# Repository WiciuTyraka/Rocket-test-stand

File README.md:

# Rocket test stand

## About
This is a project of rocket test stand to measure the trust and temperature of the engine and to save the data on SD-card. In nearly future I will add a wireless communication with computer to collect and proces data in real time. To wireless communication i will use a LoRa module.

- [Rocket test stand](#rocket-test-stand)
  * [About](#about)
  *  [PCB](#pcb)
      - [Schema](#schema)
      - [Board](#board)
      - [Libraries](#libraries)
  * [Sensors](#sensors)
      - [SD-card](#sd-card)
      - [Load cell and HX711](#load-cell-and-hx711)
      - [Thermocouples and max6675](#thermocouples-and-max6675)
      - [LoRa module](#lora-module)
      - [Pin map](#pin-map)
  * [Code for arduino](#code-for-arduino)
  * [Code for STM32](#code-for-stm32)

## PCB
Circut board is designed in Eagle

### Schema
 Rocket test stend consist of two board.
 - First board is a shield for Arduino Uno or STM32 Nucelo board. On this board is located a adpter for SD-card, amplifire for load cell and thermometr, and also a LoRa module.<br/>
[schema of rocket test stand board](https://github.com/WiciuTyraka/Rocket-test-stand/blob/master/PCB/Schema/Rocekt_test_stand.sch)

- Second board is used to collecting signals from sensors and ignite the engine.<br/>
[schema of input rocket test stand board](https://github.com/WiciuTyraka/Rocket-test-stand/blob/master/PCB/Schema/Rocekt_test_stand_input.sch)

### Board
links for downloading a board file.
- [link for rocket_test_stend.brd](https://github.com/WiciuTyraka/Rocket-test-stand/blob/master/PCB/Board/Rocekt_test_stand.brd)
- [link for rocket_test_stend_input.brd](https://github.com/WiciuTyraka/Rocket-test-stand/blob/master/PCB/Board/Rocekt_test_stand_input.brd)

### Libraries
Here are a necessary libraries for elements thats are used in project.
- [ark 8.5mm](https://github.com/WiciuTyraka/Rocket-test-stand/blob/master/PCB/Lib/111_ark_8.5mm.lbr)
- [hx711](https://github.com/WiciuTyraka/Rocket-test-stand/blob/master/PCB/Lib/111_hx711.lbr)
- [LoRa module](https://github.com/WiciuTyraka/Rocket-test-stand/blob/master/PCB/Lib/111_LORA.lbr)
- [max6675](https://github.com/WiciuTyraka/Rocket-test-stand/blob/master/PCB/Lib/111_max6675.lbr)
- [microsd](https://github.com/WiciuTyraka/Rocket-test-stand/blob/master/PCB/Lib/111_microsd.lbr)

## Sensors
In this project are used few sensors and device, here you can find a exemple code, libraries and datasheet for them.

### SD-card
---
Micro sd-card adapter is used for saving all data in txt file or as a json.
<details>
<summary>details</summary>
</br>

#### Wireing schema
This is the schema for all the wireing with arduino

#### Adapter wireing
| MicroSD Card Adapter | Adruino UNO Pin |
|----------------------|----------------:|
|          CS          |        4        |
|          SCK         |        13       |
|          MOSI        |        11       |
|          MISO        |        12       |
|          VCC         |        5V       |
|          GND         |        GND      |

#### Arduino code
[the necessary code is here](https://github.com/WiciuTyraka/Rocket-test-stand/blob/master/Sensors/SD-card/save_to_file/save_to_file.ino)
</details>

### Load cell and HX711
---
Load cell id used for measuring a engine thrust. Analog signal form load cell is converting to digital by HX711 amplifier
<details>
<summary>details</summary>
</br>
I cant find a datasheet for my chinese load cell so made this table

#### Basic load resistance checks
| Resistance check | Typical 350 Ω |
|------------------|--------------:|
| Ex+ to Ex-       | ~410Ω         |
| S+ to S-         | 350Ω          |
| Ex+ to S+        | ~315Ω         |
| Ex+ to S-        | ~315Ω         |
| Ex- to S+        | ~280Ω         |
| Ex- to S-        | ~280Ω         |

#### Load cell wireing
| HX711 | Load cell |
|-------|----------:|
| E+    | white     |
| E-    | red       |
| S+    | black     |
| S-    | green     |

#### Amplifer schema
This is a schema for all the wireing with arduino

#### HX711 library
You can download the necessary library here:
[download](https://halckemy.s3.amazonaws.com/uploads/attachments/392655/HX711-master.zip)

#### Arduino code
All the code necessary for calibration the load cell and measuring the force:
- calibration:
[the code is here](https://github.com/WiciuTyraka/Rocket-test-stand/blob/master/Sensors/Load_cell/calibration/calibration.ino)
- measurment:
[the code is here](https://github.com/WiciuTyraka/Rocket-test-stand/blob/master/Sensors/Load_cell/measurment/measurment.ino)

#### Datasheet
[link](https://circuits4you.com/wp-content/uploads/2016/11/hx711_datasheet_english.pdf)
</details>

### Thermocouples and max6675
---
To measure a temperature of the combustion chember and nozzle I'm using a thermocouple. Analog signal from this sensor is converting to digital by max6675 amplifier

<details>
<summary>details</summary>
</br>

#### Specifications of max6675
|                        |                    |
|------------------------|-------------------:|
| Suply Voltage          | 3.3 to 5 VDC       |
| Operating Current      | ~50mA              |
| Measurement Range      | 0 - 1024^∘C        |
| Measurement Resolution | +/- 0.25^∘C        |
| Output                 | Uses SPI interface |
| Required sensor        | K Thermocouple     |

#### Thermocouples schema
This is the schema for all the wireing with arduino

#### MAX6675 library
You can download the necessary library here:
[download](https://github.com/adafruit/MAX6675-library)

#### Arduino code
Basic code for reading temperature
[the necessary code is here](https://github.com/WiciuTyraka/Rocket-test-stand/blob/master/Sensors/Thermocouple/thermocouples/thermocouples.ino)

#### Datasheet
[link](http://henrysbench.capnfatz.com/wp-content/uploads/2015/05/MAX6675-Datasheet.pdf)

</details>

### LoRa module
---
I used LoRa transceiver to ignite the engine from safe distance also wireless communication allows me to watch data in real time.

<details>
<summary>details</summary>
</br>

The chip I used in project is a RFM95W transceiver.
The  RFM95W transceivers  feature  the  LoRaTM  long range modem that provides ultra-long range spread spectrum communication and high interference immunity whilst minimising current consumption.

#### RFM95W schema
This is the schema for all the wireing with arduino

#### RFM95W library
You can download the necessary library here:
[download](https://github.com/PaulStoffregen/RadioHead)

#### Arduino code
Here is a code for a transmiter and reciver(in fact both of them are transceivers) :
- transmiter:
[the code is here](https://github.com/WiciuTyraka/Rocket-test-stand/blob/master/Sensors/LoRa/transmiter/transmiter.ino)
- reciver:
[the code is here](https://github.com/WiciuTyraka/Rocket-test-stand/blob/master/Sensors/LoRa/reciver/reciver.ino)

#### Datasheet
[link](https://www.hoperf.com/modules/lora/RFM95.html)

</details>

### Pin map
---
This table contains information abaout all pins to witch are connected device

| Pin number |Device     |
|------------|---------- |
| 0          |LoRa DIO0  |
| 1          |LoRa DIO1  |
| 2          |HX711 CLK  |
| 3          |HX711 DOUT |
| 4          |SD card    |
| 5          |LoRa RESET |
| 6          |LoRa CS    |
| 8          |max6675 CS |
| 9          |max6675 SO |
| 10         |max6675 SCK|
| 11         |MOSI       |
| 12         |MISO       |
| 13         |CLK        |
| 14         |switch     |
| 15         |led        |
| 16         |ignite     |
| 17         |buzzer     |

## Code for Arduino

This version of code not include a wireless communication
- here you can find a [code](https://github.com/WiciuTyraka/Rocket-test-stand/blob/master/Arduino_code/Rocekt_test_stand/Rocekt_test_stand.ino)

## Code for STM32
cause i'm very busy right now, i'll back to this task in nearly future.

*by* Wiktor Tasarek

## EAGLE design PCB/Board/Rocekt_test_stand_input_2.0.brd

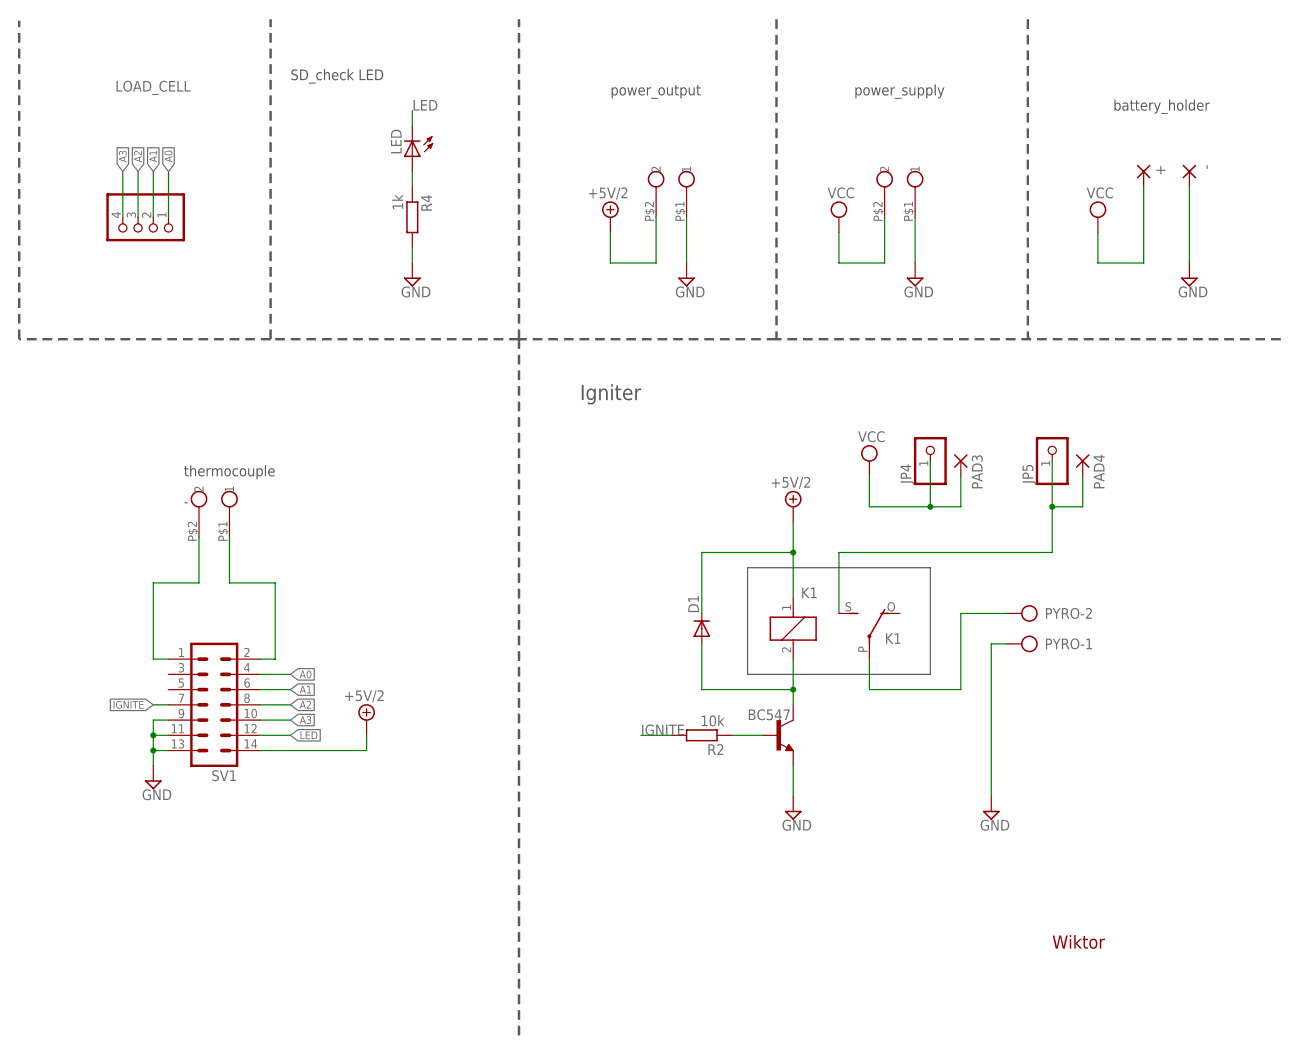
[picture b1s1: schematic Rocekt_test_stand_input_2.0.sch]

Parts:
+: SMD5; SMD2,54-5,08
-: SMD5; SMD2,54-5,08
D1: 1N4004; DO41-10
JP4, JP5: PINHD-1X1; 1X01
K1: G5L; G5LE
LED: LED_ELD260; LED_LD260
LOAD_CELL: PINHD-1X4; 1X04
PAD3, PAD4: SMD2; SMD1,27-2,54
POWER_SUPPLY, POWER_SUPPLY1: ARK_8.5MM; ZLACZESRUBOWE8.5MM
PYRO: AK500/2
R2: 10k; 0204/5
R4: 1k; 0204/5
SV1: ML14
T1: BC547; TO92
U$1: ARK_8.5MM; ZLACZESRUBOWE8.5MM

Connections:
+5V/2: D1.C, K1.1, POWER_SUPPLY1.P$2 (2), SV1.14
-: SV1.1, U$1.P$2 (2)
A0: LOAD_CELL.1, SV1.4
A1: LOAD_CELL.2, SV1.6
A2: LOAD_CELL.3, SV1.8
A3: LOAD_CELL.4, SV1.10
GND: -.1, POWER_SUPPLY.P$1 (1), POWER_SUPPLY1.P$1 (1), PYRO.1, R4.2, SV1.9, SV1.11, SV1.13, T1.1 (E)
IGNITE: R2.2, SV1.7
LED: LED.K (C), SV1.12
unnamed: D1.A, K1.2, T1.3 (C)
unnamed: R2.1, T1.2 (B)
unnamed: K1.P, PYRO.2
unnamed: SV1.2, U$1.P$1 (1)
unnamed: LED.A, R4.1
unnamed: JP5.1, K1.S, PAD4.1
VCC: +.1, JP4.1, PAD3.1, POWER_SUPPLY.P$2 (2)

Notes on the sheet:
thermocouple
power_supply
Wiktor
battery_holder
power_output
SD_check LED
Igniter

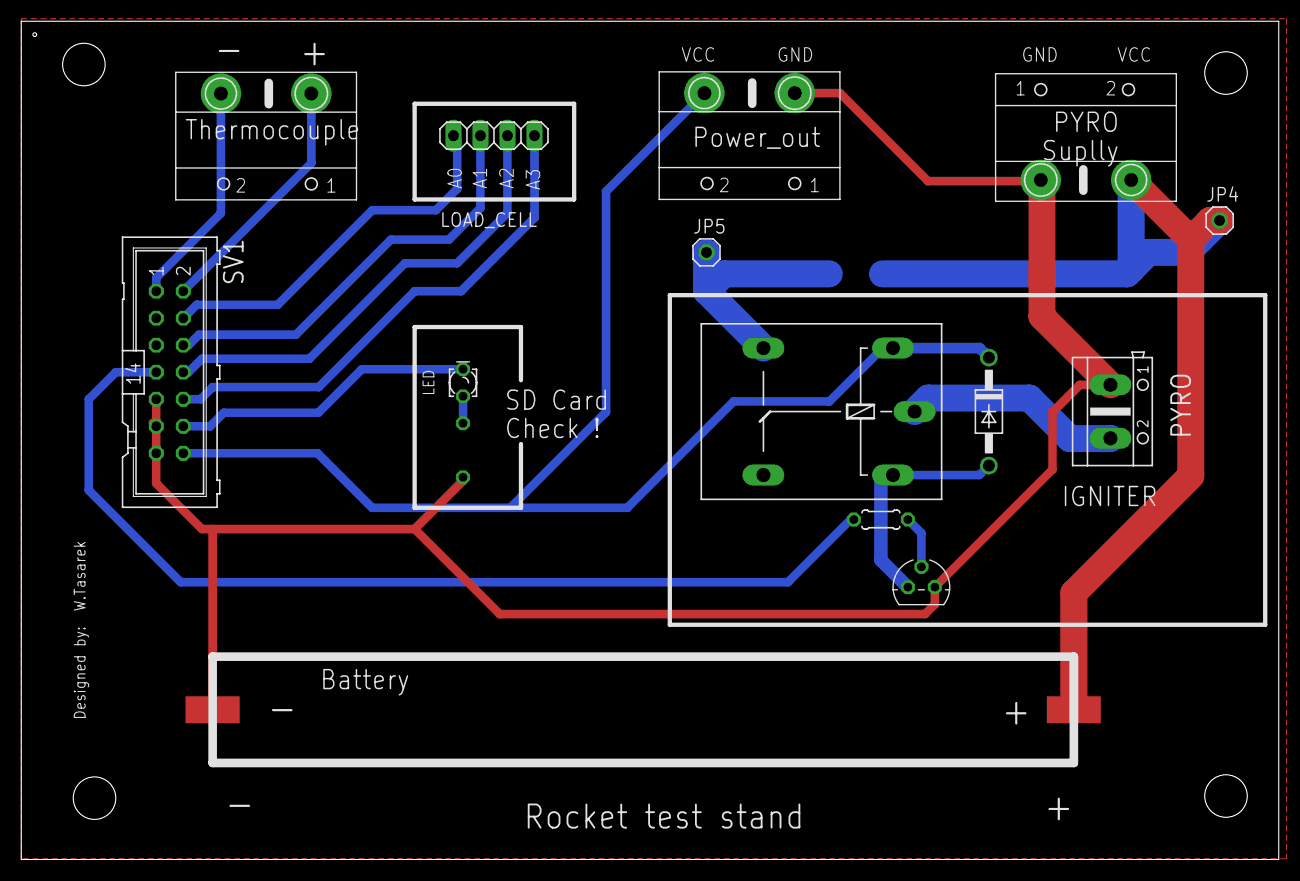
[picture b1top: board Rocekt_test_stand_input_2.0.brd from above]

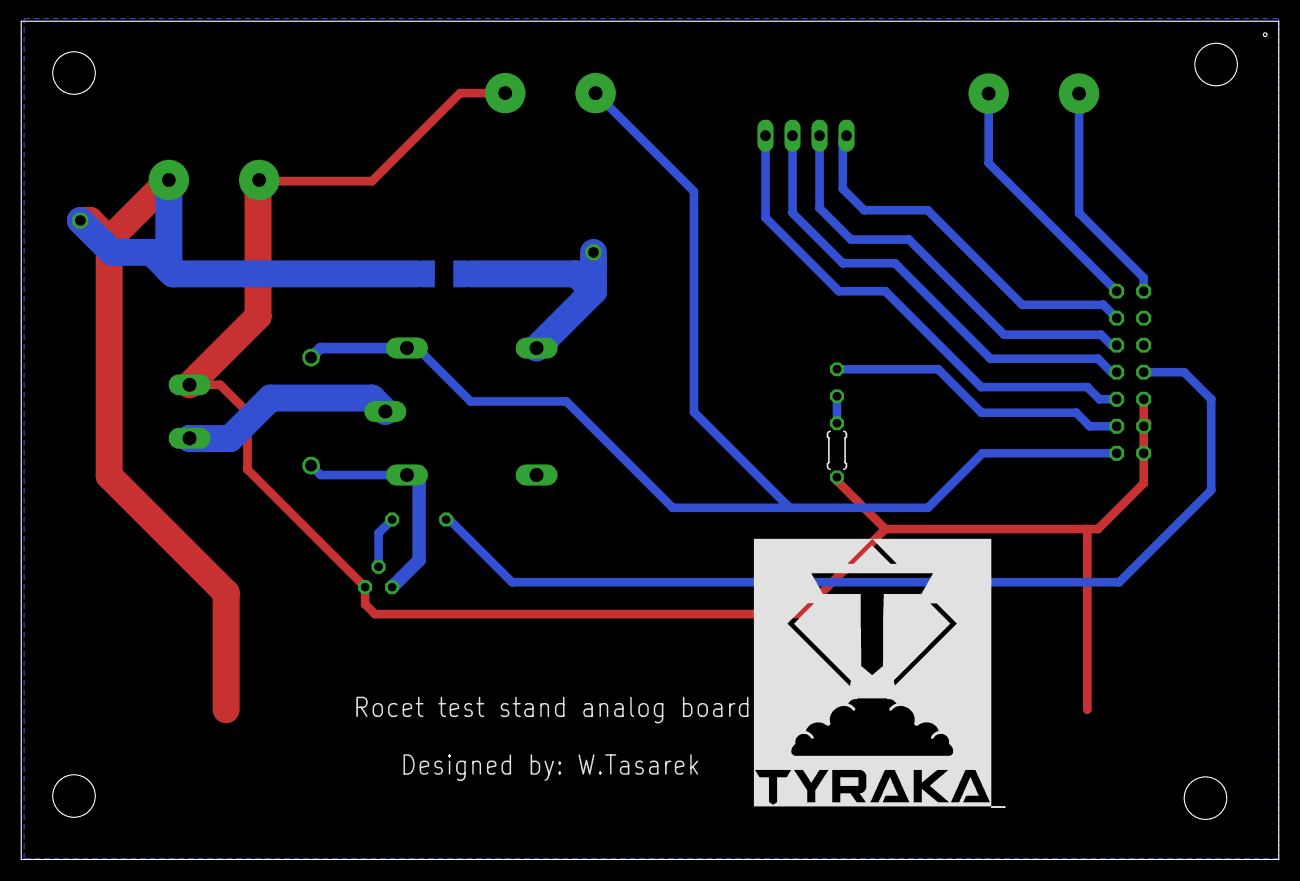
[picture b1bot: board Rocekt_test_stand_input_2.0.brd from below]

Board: 2 copper layers, 118.3 x 78.8 mm, 18 parts (3 on the bottom side), 16 nets.

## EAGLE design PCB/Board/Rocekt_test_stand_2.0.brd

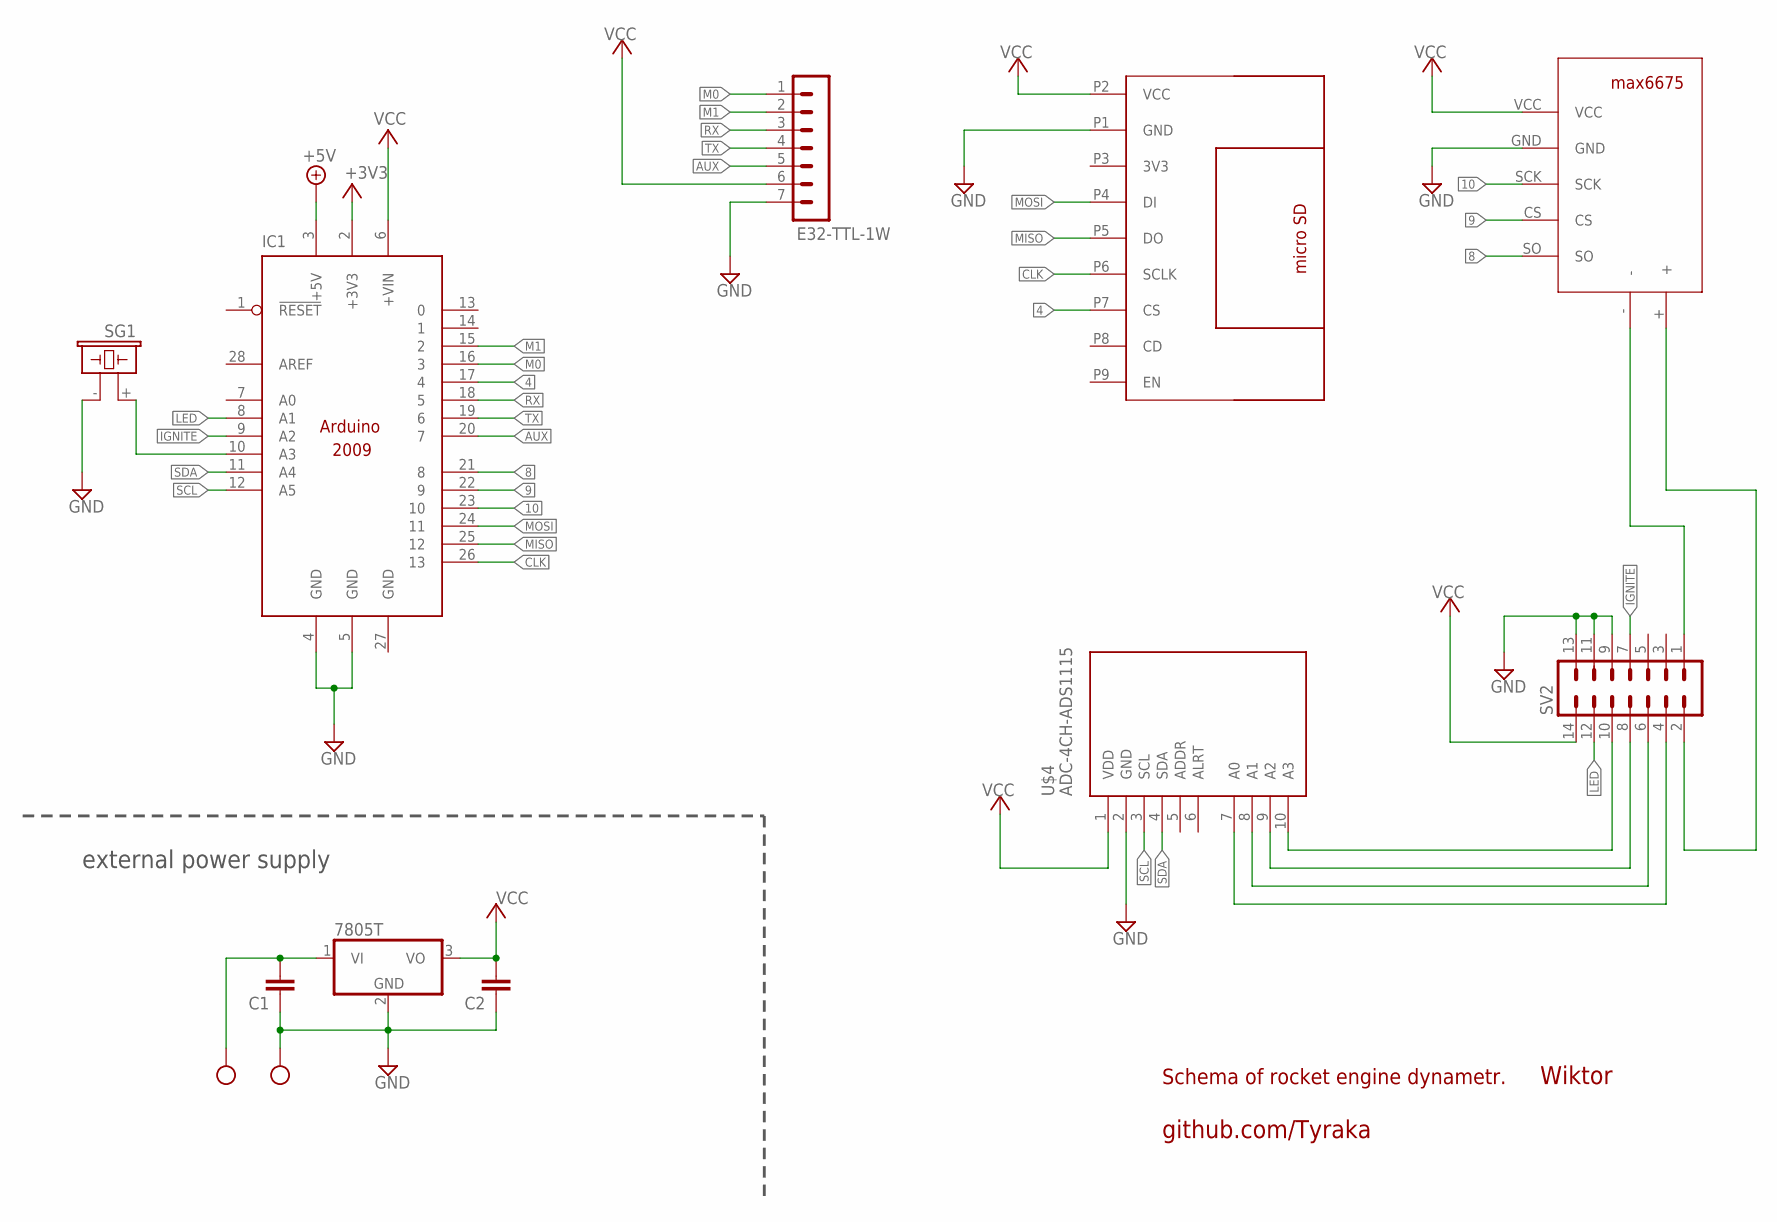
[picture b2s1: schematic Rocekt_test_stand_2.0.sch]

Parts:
C1, C2: C2.5/4; C2.5-4
E32-TTL-1W: MA07-1
IC1: ARDUINO2009_10; ARDUINO2009
IC2: 7805T; TO220H
SD1: MICRO_SD
SG1: F/CM12P
SV2: ML14
U$2: MAX6675; MAX6675_FOOTPRINT
U$4: ADC-4CH-ADS1115
X1: AK300/2

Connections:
4: IC1.17 (4), SD1.P7 (CS)
8: IC1.21 (8), U$2.SO
9: IC1.22 (9), U$2.CS
10: IC1.23 (10), U$2.SCK
+3V3: IC1.2 (+3V3)
+5V: IC1.3 (+5V)
AUX: E32-TTL-1W.5, IC1.20 (7)
CLK: IC1.26 (13), SD1.P6 (SCLK)
GND: C1.1, C2.1, E32-TTL-1W.7, IC1.4 (GND), IC1.5 (GND), IC1.27 (GND), IC2.2 (GND), SD1.P1 (GND), SG1.- (2), SV2.9, SV2.11, SV2.13, U$2.GND, U$4.2 (GND), X1.2
IGNITE: IC1.9 (A2), SV2.7
LED: IC1.8 (A1), SV2.12
M0: E32-TTL-1W.1, IC1.16 (3)
M1: E32-TTL-1W.2, IC1.15 (2)
MISO: IC1.25 (12), SD1.P5 (DO)
MOSI: IC1.24 (11), SD1.P4 (DI)
unnamed: SV2.2, U$2.+
unnamed: IC1.10 (A3), SG1.+ (1)
unnamed: SV2.1, U$2.-
unnamed: SV2.4, U$4.7 (A0)
unnamed: SV2.10, U$4.10 (A3)
unnamed: SV2.8, U$4.9 (A2)
unnamed: SV2.6, U$4.8 (A1)
unnamed: C1.2, IC2.1 (VI), X1.1
RX: E32-TTL-1W.3, IC1.18 (5)
SCL: IC1.12 (A5), U$4.3 (SCL)
SDA: IC1.11 (A4), U$4.4 (SDA)
TX: E32-TTL-1W.4, IC1.19 (6)
VCC: C2.2, E32-TTL-1W.6, IC1.6 (+VIN), IC2.3 (VO), SD1.P2 (VCC), SV2.14, U$2.VCC, U$4.1 (VDD)

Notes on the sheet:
Wiktor
Schema of rocket engine dynametr.
github.com/Tyraka
external power supply

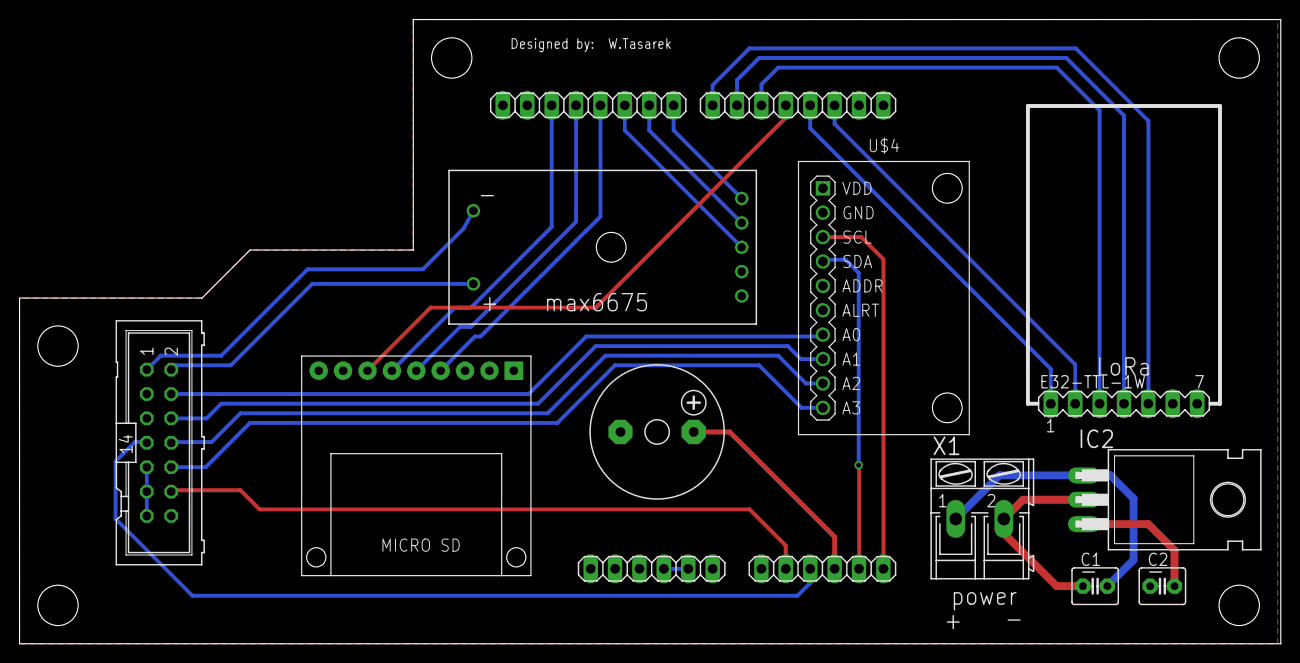
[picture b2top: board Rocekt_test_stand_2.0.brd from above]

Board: 2 copper layers, 131.3 x 65.0 mm, 11 parts (0 on the bottom side), 26 nets.

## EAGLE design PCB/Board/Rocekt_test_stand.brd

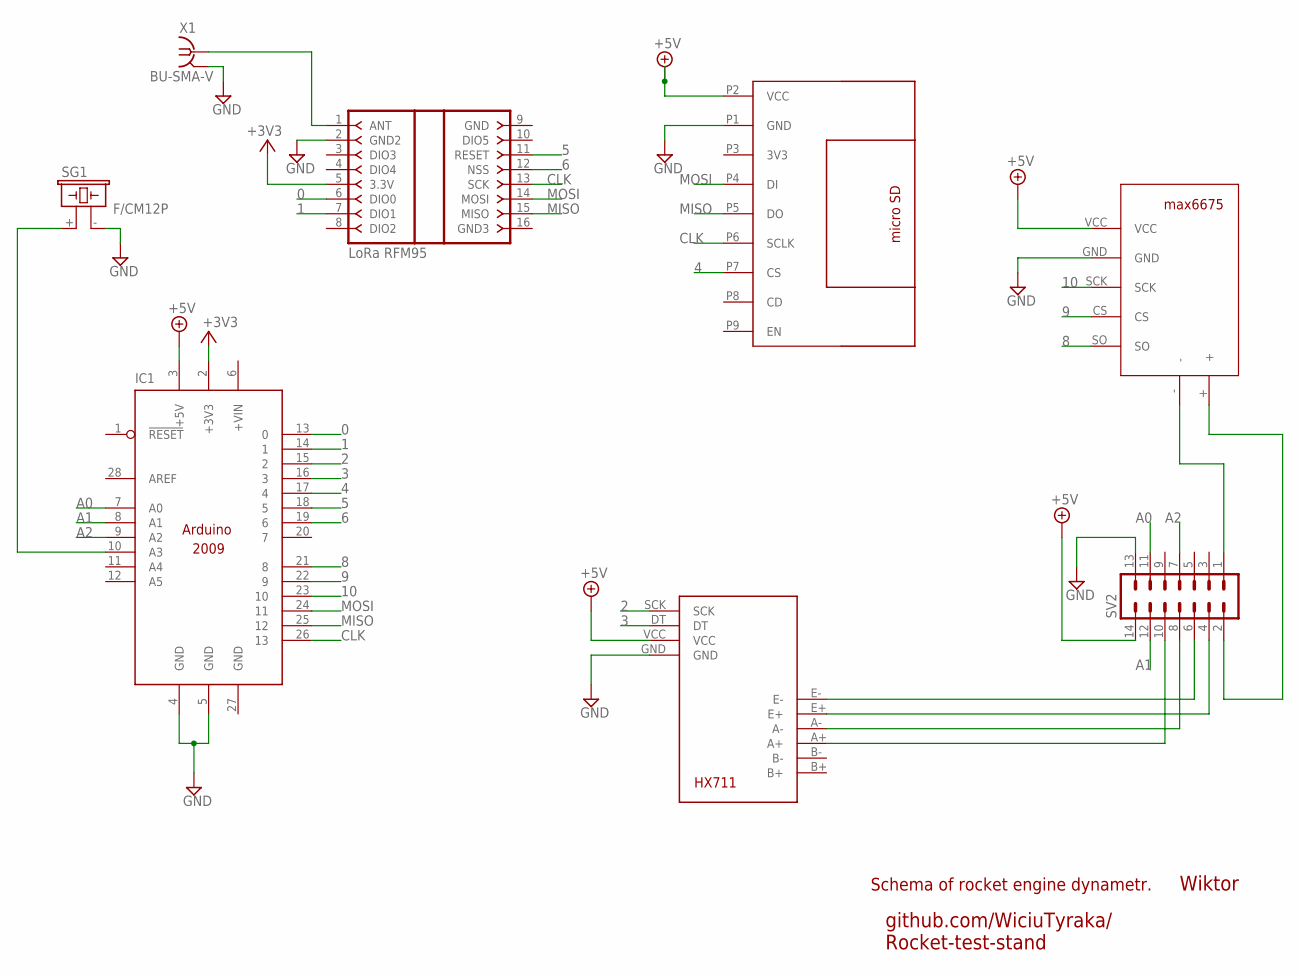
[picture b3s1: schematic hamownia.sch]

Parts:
IC1: ARDUINO2009_10; ARDUINO2009
LORA: LORA_RFM95_ADAPTERLORA_RFM95W; LORA_RFM95_ADAPTER
SD1: MICRO_SD
SG1: F/CM12P
SV2: ML14
U$1: HX711
U$2: MAX6675; MAX6675_FOOTPRINT
X1: BU-SMA-V

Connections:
0: IC1.13 (0), LORA.6 (DIO0)
1: IC1.14 (1), LORA.7 (DIO1)
2: IC1.15 (2), U$1.SCK
3: IC1.16 (3), U$1.DT
4: IC1.17 (4), SD1.P7 (CS)
5: IC1.18 (5), LORA.11 (RESET)
6: IC1.19 (6), LORA.12 (NSS)
8: IC1.21 (8), U$2.SO
9: IC1.22 (9), U$2.CS
10: IC1.23 (10), U$2.SCK
+3V3: IC1.2 (+3V3), LORA.5 (3.3V)
+5V: IC1.3 (+5V), SD1.P2 (VCC), SV2.14, U$1.VCC, U$2.VCC
A0: IC1.7 (A0), SV2.11
A1: IC1.8 (A1), SV2.12
A2: IC1.9 (A2), SV2.7
CLK: IC1.26 (13), LORA.13 (SCK), SD1.P6 (SCLK)
GND: IC1.4 (GND), IC1.5 (GND), IC1.27 (GND), LORA.2 (GND2), SD1.P1 (GND), SG1.- (2), SV2.13, U$1.GND, U$2.GND, X1.2, X1.3 (2), X1.4 (2), X1.5 (2)
MISO: IC1.25 (12), LORA.15 (MISO), SD1.P5 (DO)
MOSI: IC1.24 (11), LORA.14 (MOSI), SD1.P4 (DI)
unnamed: SV2.2, U$2.+
unnamed: IC1.10 (A3), SG1.+ (1)
unnamed: SV2.1, U$2.-
unnamed: SV2.4, U$1.E+
unnamed: SV2.6, U$1.E-
unnamed: SV2.8, U$1.A-
unnamed: LORA.1 (ANT), X1.1
unnamed: SV2.10, U$1.A+

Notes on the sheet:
Wiktor
Schema of rocket engine dynametr.
github.com/WiciuTyraka/ Rocket-test-stand

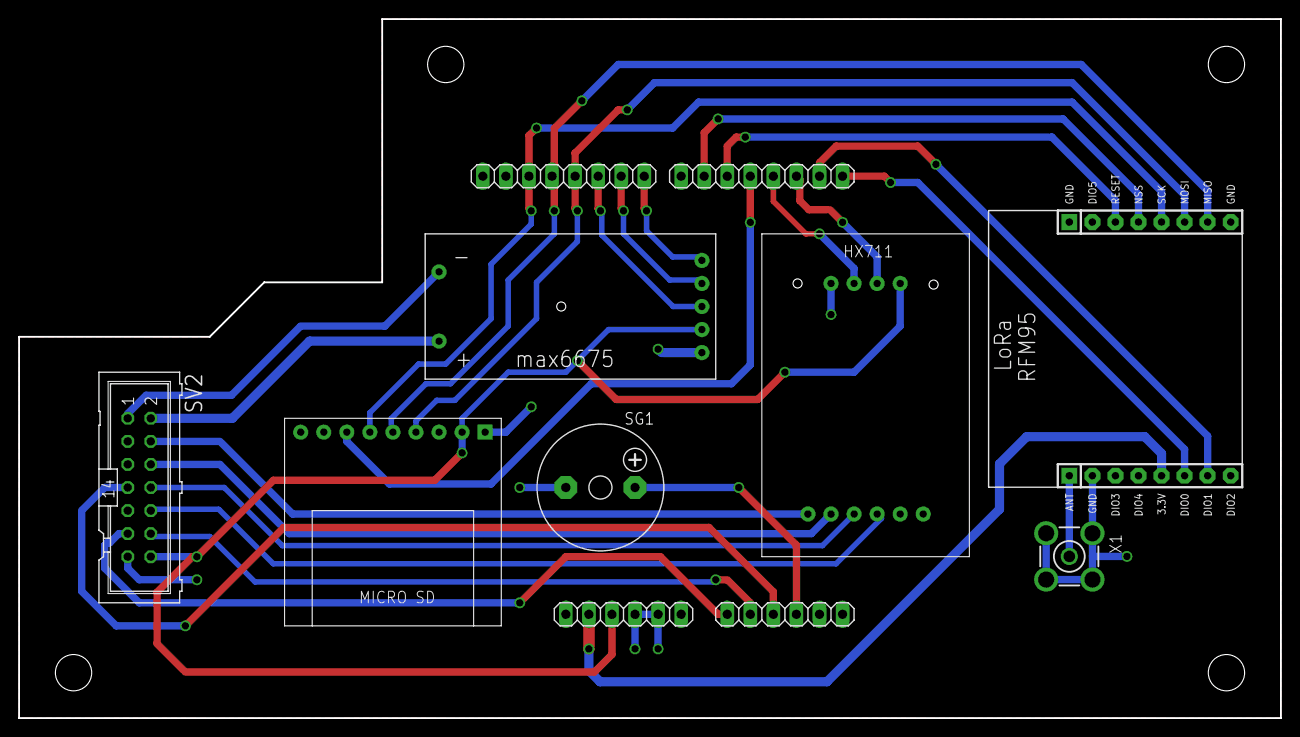
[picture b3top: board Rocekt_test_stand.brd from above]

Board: 2 copper layers, 139.0 x 77.0 mm, 8 parts (0 on the bottom side), 27 nets.

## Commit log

2019-05-07 upgrade
2019-05-07 pcb menu
2019-05-07 menu
2019-05-07 blank
2019-05-07 another blank
2019-05-07 <br/> blank
2019-05-08 add link
2019-05-08 link add
2019-05-08 sd add
2019-05-08 menu fix
2019-05-08 sd fix
2019-05-08 drop down
2019-05-08 drop dwon menu
2019-05-08 sd-card
2019-05-08 details sd card
2019-05-08 lloadcell
2019-05-08 loadcell
2019-05-08 loadcelll
2019-05-08 downgrade
2019-05-08 loadcaall hx711
2019-05-08 fix menu
2019-05-08 anchor
2019-05-08 thermocouples
2019-05-08 thermocoupes fix
2019-05-08 lora
2019-05-08 ----- add
2019-05-08 code
2019-05-08 signature
2019-05-08 deatil fix
2019-05-08 pin map
2019-05-08 add libraries
2019-05-08 lora upgrade
2019-05-08 add lib
2019-05-08 add code link
2019-05-08 add lib and arduino code
2019-05-08 code add
2019-05-08 arduino code
2019-05-08 board fix
2019-05-09 board
2019-05-09 add radiohead library
2019-05-09 pin map add
2020-01-02 plytki na inynierke
    plytki na inzynierke

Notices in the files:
parts and their libraries:
ads1115: Released under the Creative Commons Attribution 4.0 International License: http://creativecommons.org/licenses/by/4.0
